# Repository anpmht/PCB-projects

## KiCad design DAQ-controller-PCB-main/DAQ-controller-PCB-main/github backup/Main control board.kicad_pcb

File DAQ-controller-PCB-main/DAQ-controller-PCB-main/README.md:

# DAQ-controller-PCB
### main controller - teenssy_4.1
### mux IC - 74HCT154PW
### Controls 16 channel analog amplifier and four ADC using  74HCT154PW multiplexer.

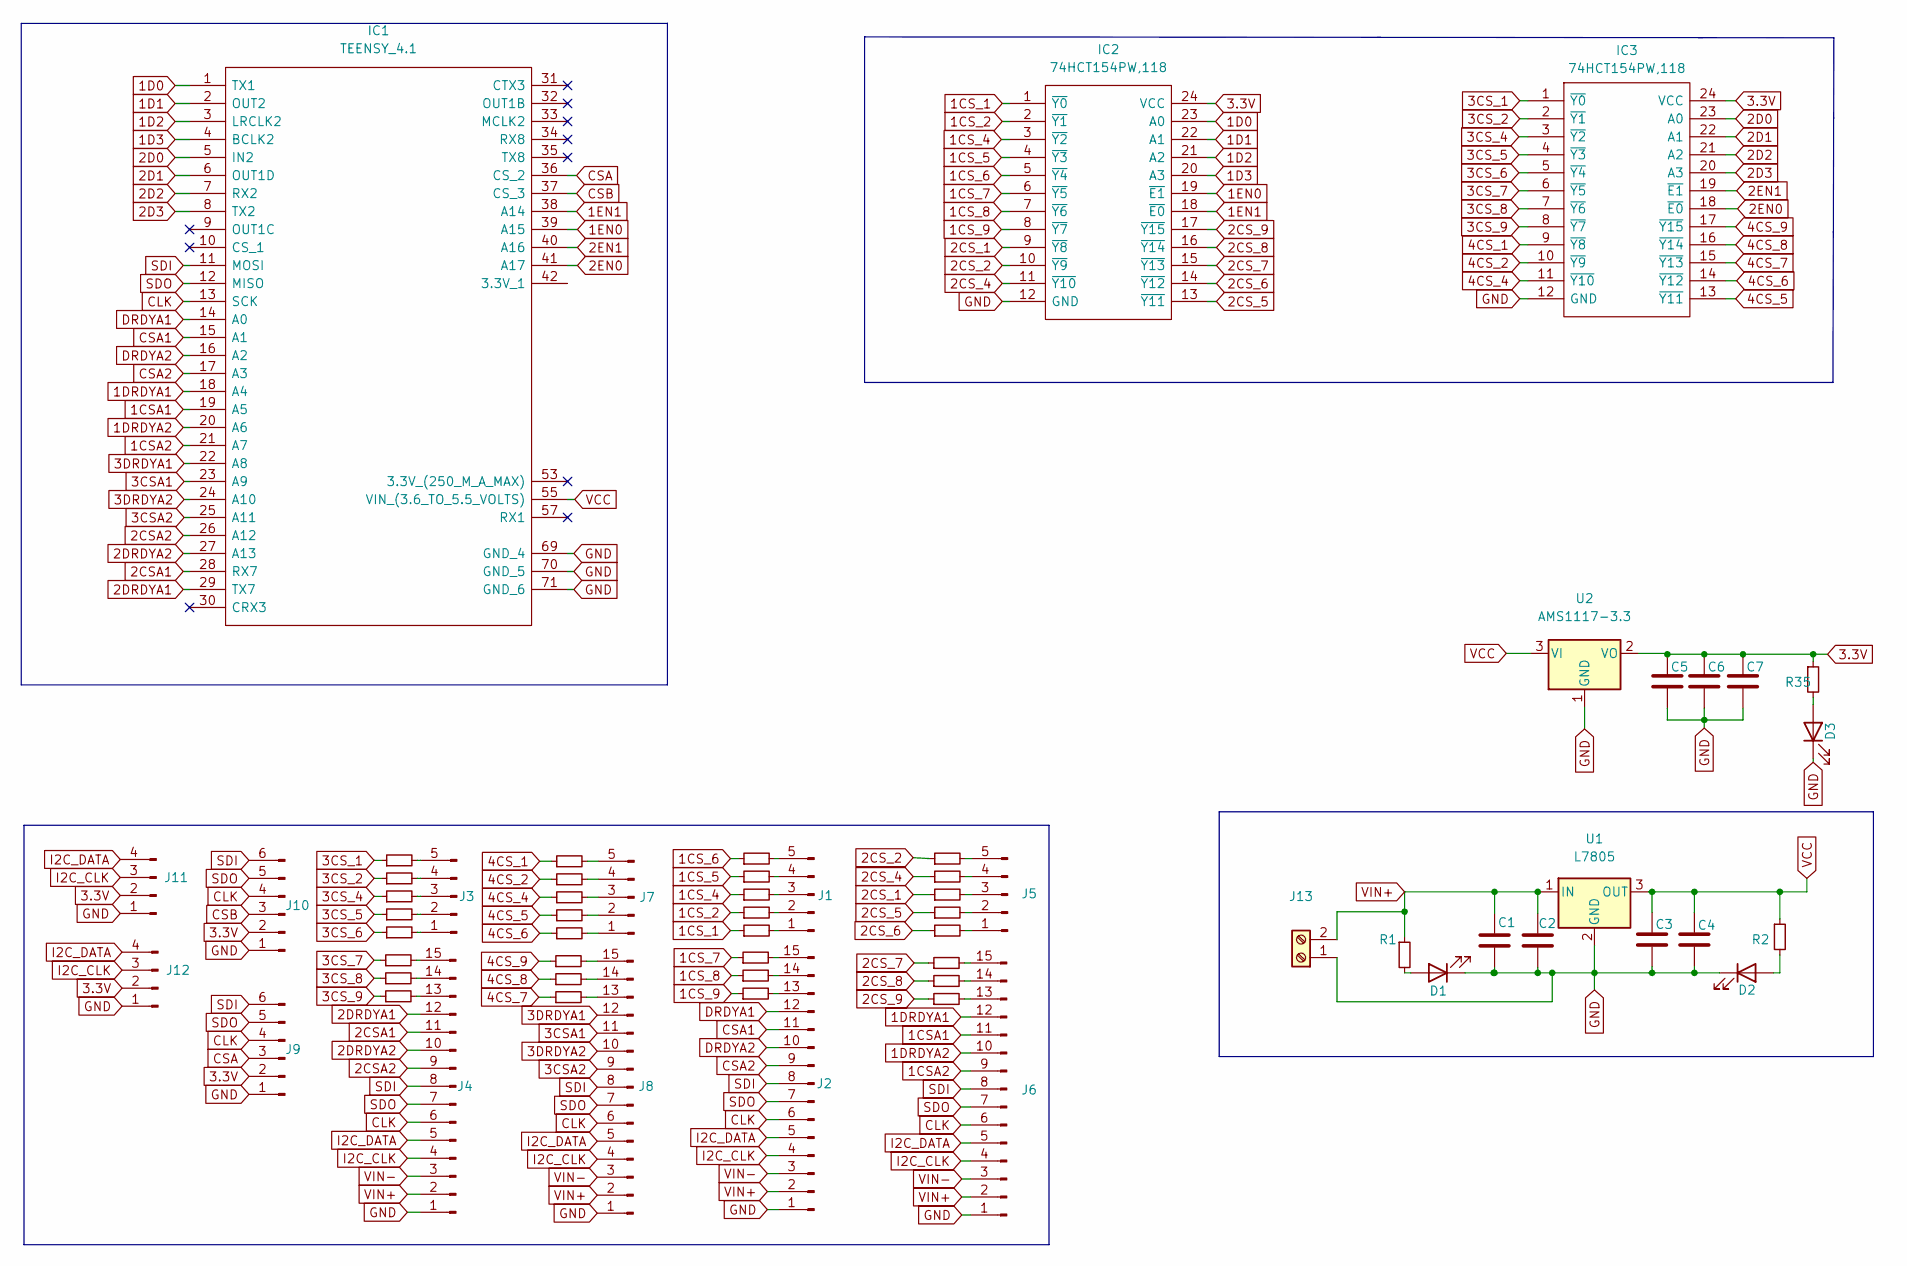
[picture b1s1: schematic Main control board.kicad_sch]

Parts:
C1, C3: 10uf; C_0805_2012Metric
C2, C4, C5, C6, C7: 1uf; C_0603_1608Metric
D1, D2, D3: LED; LED_0603_1608Metric
IC1: TEENSY_4.1; TEENSY41; Manufacturer_Part_Number TEENSY 4.1
IC2, IC3: 74HCT154PW,118; SOP65P640X110-24N; Manufacturer_Part_Number 74HCT154PW,118; Mouser Part Number 771-HCT154PW118
J1, J3, J5, J7: Conn_01x05_Male; JST_EH_B5B-EH-A_1x05_P2.50mm_Vertical
J2, J4, J6, J8: Conn_01x15_Male; JST_EH_B15B-EH-A_1x15_P2.50mm_Vertical
J9, J10: Conn_01x06_Male; JST_EH_B6B-EH-A_1x06_P2.50mm_Vertical
J11, J12: Conn_01x04_Male; JST_EH_B4B-EH-A_1x04_P2.50mm_Vertical
J13: (no value)
R1, R2, R35: 1.5k; R_0603_1608Metric
R3, R4, R5, R6, R7, R8, R9, R10, R11, R12, R13, R14, R15, R16, R17, R18, R19, R20, R21, R22, R23, R24, R25, R26, R27, R28, R29, R30, R31, R32, R33, R34: 470; R_0603_1608Metric
U1: L7805; TO228P972X240-3N
U2: AMS1117-3.3; SOT-223-3_TabPin2

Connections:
1CSA1: IC1.19 (A5), J6.11
1CSA2: IC1.21 (A7), J6.9
1CS_1: IC2.1 (~Y0), R26.1
1CS_2: IC2.2 (~Y1), R25.1
1CS_4: IC2.3 (~Y2), R24.1
1CS_5: IC2.4 (~Y3), R23.1
1CS_6: IC2.5 (~Y4), R22.1
1CS_7: IC2.6 (~Y5), R19.1
1CS_8: IC2.7 (~Y6), R20.1
1CS_9: IC2.8 (~Y7), R21.1
1D0: IC1.1 (TX1), IC2.23 (A0)
1D1: IC1.2 (OUT2), IC2.22 (A1)
1D2: IC1.3 (LRCLK2), IC2.21 (A2)
1D3: IC1.4 (BCLK2), IC2.20 (A3)
1DRDYA1: IC1.18 (A4), J6.12
1DRDYA2: IC1.20 (A6), J6.10
1EN0: IC1.39 (A15), IC2.19 (~E1)
1EN1: IC1.38 (A14), IC2.18 (~E0)
2CSA1: IC1.28 (RX7), J4.11
2CSA2: IC1.26 (A12), J4.9
2CS_1: IC2.9 (~Y8), R32.1
2CS_2: IC2.10 (~Y9), R30.1
2CS_4: IC2.11 (~Y10), R31.1
2CS_5: IC2.13 (~Y11), R33.1
2CS_6: IC2.14 (~Y12), R34.1
2CS_7: IC2.15 (~Y13), R27.1
2CS_8: IC2.16 (~Y14), R28.1
2CS_9: IC2.17 (~Y15), R29.1
2D0: IC1.5 (IN2), IC3.23 (A0)
2D1: IC1.6 (OUT1D), IC3.22 (A1)
2D2: IC1.7 (RX2), IC3.21 (A2)
2D3: IC1.8 (TX2), IC3.20 (A3)
2DRDYA1: IC1.29 (TX7), J4.12
2DRDYA2: IC1.27 (A13), J4.10
2EN0: IC1.41 (A17), IC3.18 (~E0)
2EN1: IC1.40 (A16), IC3.19 (~E1)
3.3V: C5.1, C6.1, C7.1, IC2.24 (VCC), IC3.24 (VCC), J9.2, J10.2, J11.2, J12.2, R35.1, U2.2 (VO)
3CSA1: IC1.23 (A9), J8.11
3CSA2: IC1.25 (A11), J8.9
3CS_1: IC3.1 (~Y0), R6.1
3CS_2: IC3.2 (~Y1), R7.1
3CS_4: IC3.3 (~Y2), R8.1
3CS_5: IC3.4 (~Y3), R9.1
3CS_6: IC3.5 (~Y4), R10.1
3CS_7: IC3.6 (~Y5), R3.1
3CS_8: IC3.7 (~Y6), R4.1
3CS_9: IC3.8 (~Y7), R5.1
3DRDYA1: IC1.22 (A8), J8.12
3DRDYA2: IC1.24 (A10), J8.10
4CS_1: IC3.9 (~Y8), R14.1
4CS_2: IC3.10 (~Y9), R15.1
4CS_4: IC3.11 (~Y10), R16.1
4CS_5: IC3.13 (~Y11), R17.1
4CS_6: IC3.14 (~Y12), R18.1
4CS_7: IC3.15 (~Y13), R13.1
4CS_8: IC3.16 (~Y14), R12.1
4CS_9: IC3.17 (~Y15), R11.1
CLK: IC1.13 (SCK), J2.6, J4.6, J6.6, J8.6, J9.4, J10.4
CSA: IC1.36 (CS_2), J9.3
CSA1: IC1.15 (A1), J2.11
CSA2: IC1.17 (A3), J2.9
CSB: IC1.37 (CS_3), J10.3
DRDYA1: IC1.14 (A0), J2.12
DRDYA2: IC1.16 (A2), J2.10
GND: C1.2, C2.2, C3.2, C4.2, C5.2, C6.2, C7.2, D1.1 (K), D2.1 (K), D3.1 (K), IC1.69 (GND_4), IC1.70 (GND_5), IC1.71 (GND_6), IC2.12 (GND), IC3.12 (GND), J2.1, J4.1, J6.1, J8.1, J9.1, J10.1, J11.1, J12.1, J13.1, U1.2 (GND), U2.1 (GND)
I2C_CLK: J2.4, J4.4, J6.4, J8.4, J11.3, J12.3
I2C_DATA: J2.5, J4.5, J6.5, J8.5, J11.4, J12.4
unnamed: D1.2 (A), R1.2
unnamed: D2.2 (A), R2.2
unnamed: D3.2 (A), R35.2
unnamed: J1.1, R26.2
unnamed: J1.2, R25.2
unnamed: J1.3, R24.2
unnamed: J1.4, R23.2
unnamed: J1.5, R22.2
unnamed: J2.13, R21.2
unnamed: J2.14, R20.2
unnamed: J2.15, R19.2
unnamed: J3.1, R10.2
unnamed: J3.2, R9.2
unnamed: J3.3, R8.2
unnamed: J3.4, R7.2
unnamed: J3.5, R6.2
unnamed: J4.13, R5.2
unnamed: J4.14, R4.2
unnamed: J4.15, R3.2
unnamed: J5.1, R34.2
unnamed: J5.2, R33.2
unnamed: J5.3, R32.2
unnamed: J5.4, R31.2
unnamed: J5.5, R30.2
unnamed: J6.13, R29.2
unnamed: J6.14, R28.2
unnamed: J6.15, R27.2
unnamed: J7.1, R18.2
unnamed: J7.2, R17.2
unnamed: J7.3, R16.2
unnamed: J7.4, R15.2
unnamed: J7.5, R14.2
unnamed: J8.13, R13.2
unnamed: J8.14, R12.2
unnamed: J8.15, R11.2
SDI: IC1.11 (MOSI), J2.8, J4.8, J6.8, J8.8, J9.6, J10.6
SDO: IC1.12 (MISO), J2.7, J4.7, J6.7, J8.7, J9.5, J10.5
VCC: C3.1, C4.1, IC1.55 (VIN_(3.6_TO_5.5_VOLTS)), R2.1, U1.3 (OUT), U2.3 (VI)
VIN+: C1.1, C2.1, J2.2, J4.2, J6.2, J8.2, J13.2, R1.1, U1.1 (IN)
VIN-: J2.3, J4.3, J6.3, J8.3

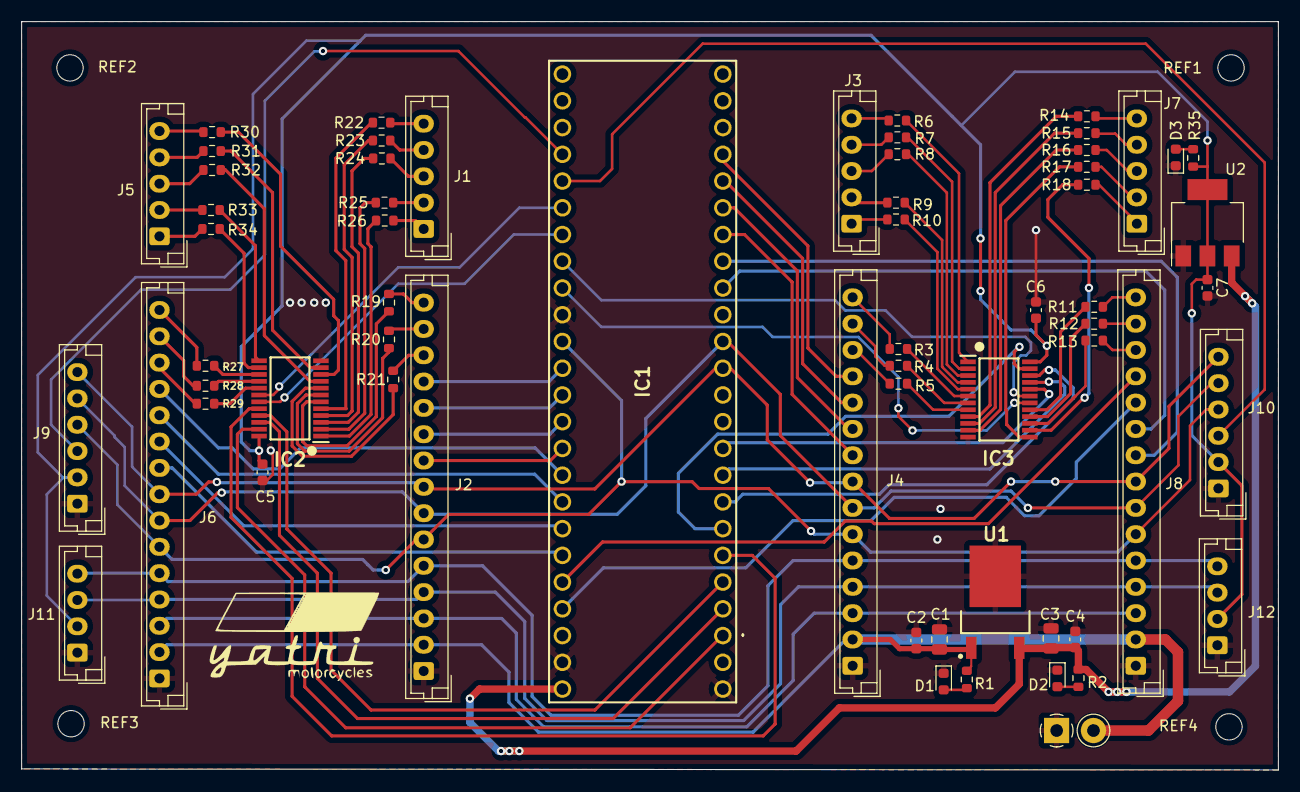
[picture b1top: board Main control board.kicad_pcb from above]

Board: 2 copper layers, 119.4 x 71.1 mm, 67 parts (0 on the bottom side), 107 nets.

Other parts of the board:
REF1, REF2, REF3, REF4: MountingHole_2.5mm

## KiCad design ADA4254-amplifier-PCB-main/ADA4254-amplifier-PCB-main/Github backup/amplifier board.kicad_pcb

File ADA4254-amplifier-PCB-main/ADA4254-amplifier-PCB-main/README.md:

# ADA4254-amplifier-PCB
ADA4254 precision amplifier PCB board

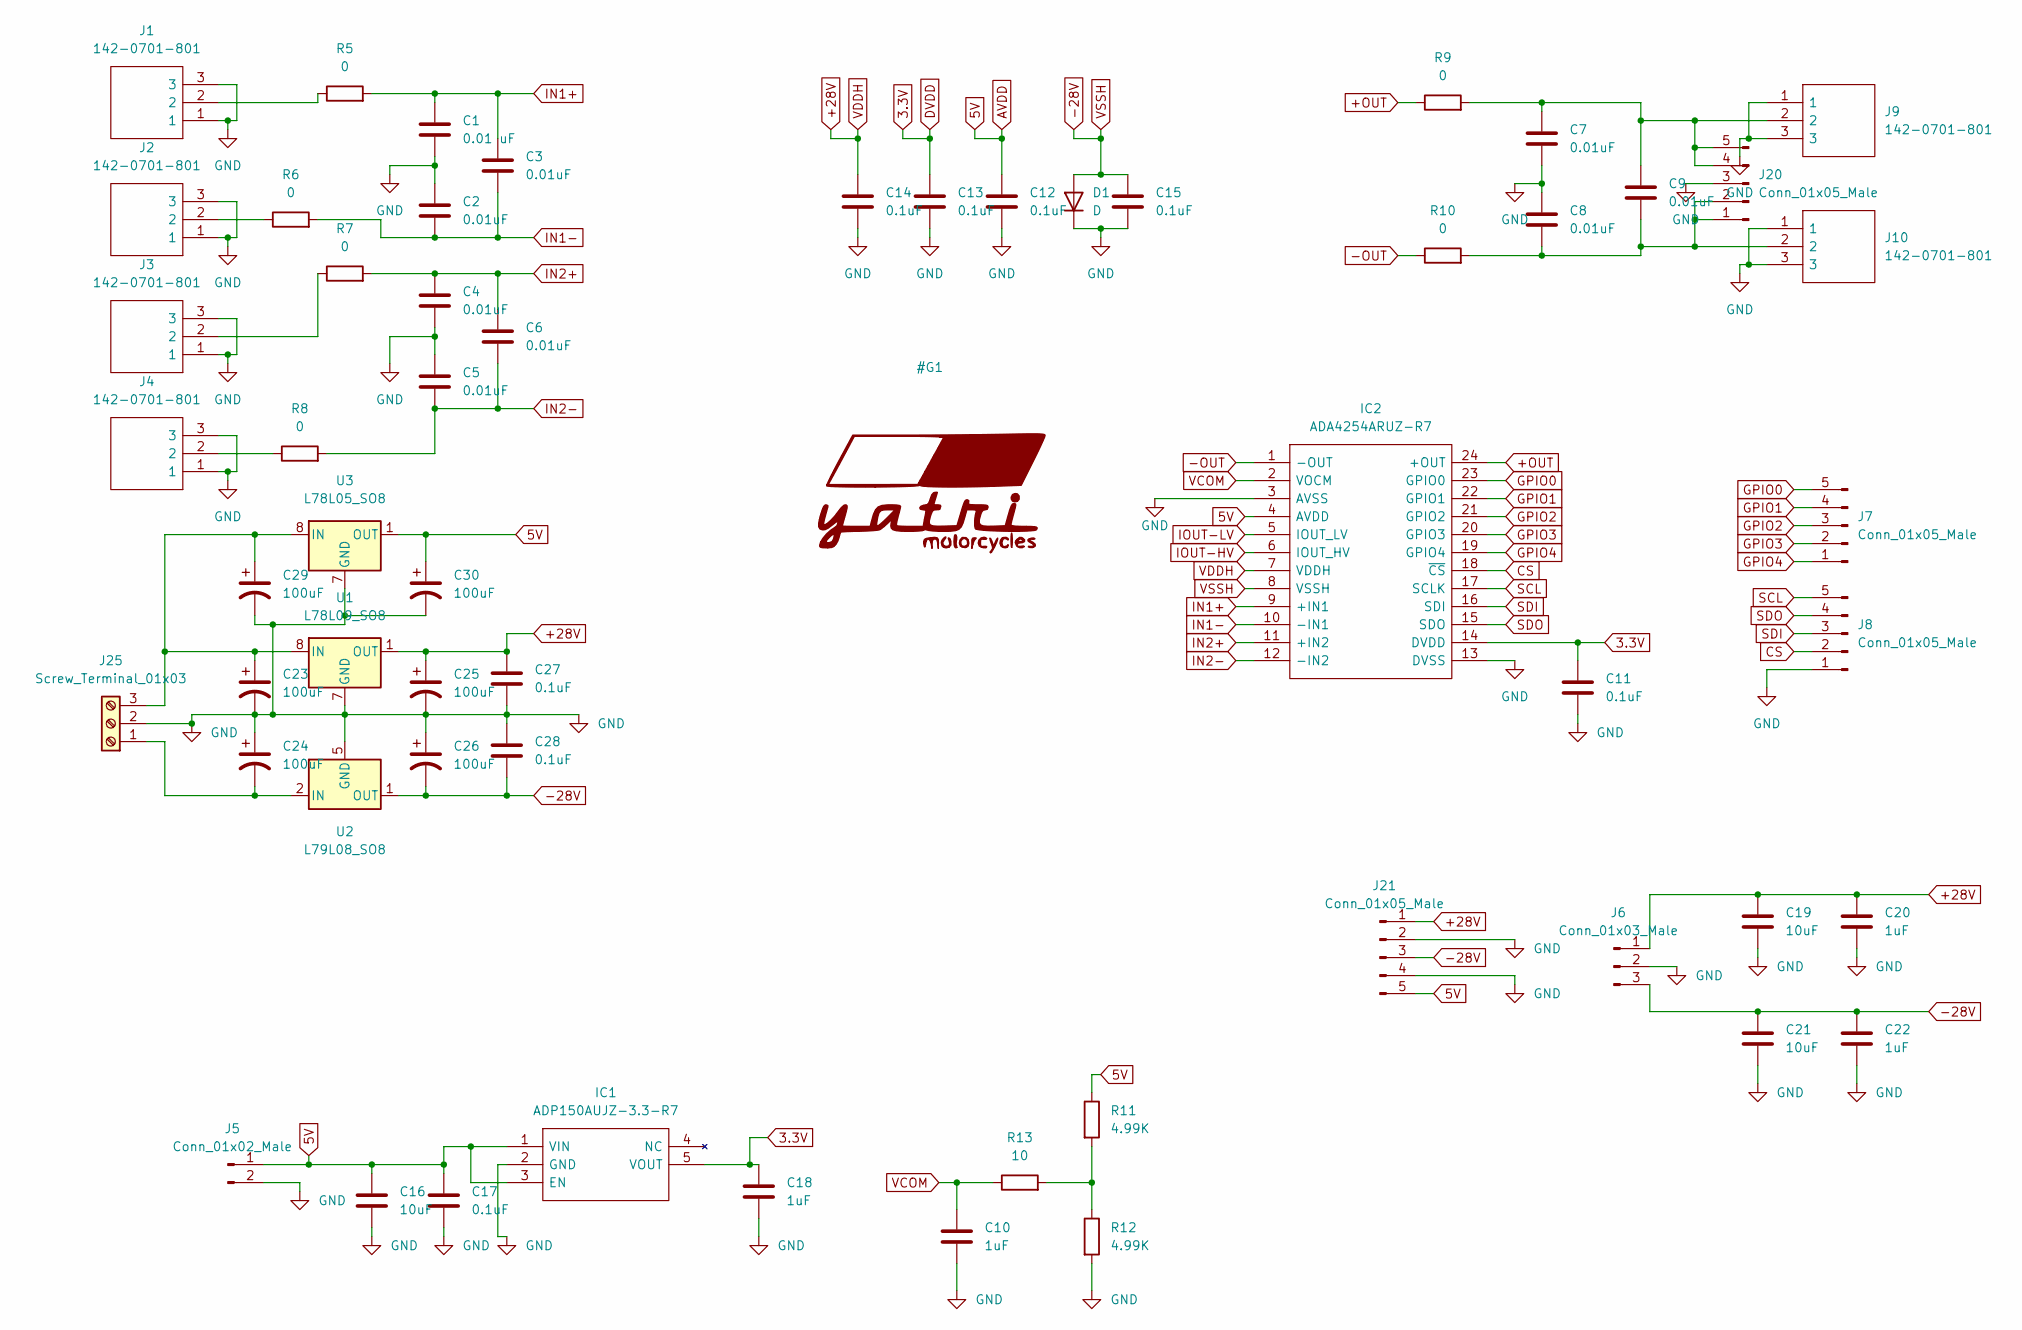
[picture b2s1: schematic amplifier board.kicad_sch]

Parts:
C1: 0.01 uF; C_0603_1608Metric_Pad1.08x0.95mm_HandSolder
C2, C3, C4, C5, C6, C7, C8, C9: 0.01uF; C_0603_1608Metric_Pad1.08x0.95mm_HandSolder
C10, C18, C20, C22: 1uF; C_0603_1608Metric_Pad1.08x0.95mm_HandSolder
C11, C12, C13, C14, C15, C17, C27, C28: 0.1uF; C_0603_1608Metric_Pad1.08x0.95mm_HandSolder
C16, C19, C21: 10uF; C_0805_2012Metric_Pad1.18x1.45mm_HandSolder
C23, C24, C25, C26, C29, C30: 100uF; CP_Radial_D6.3mm_P2.50mm
D1: D; D_0603_1608Metric_Pad1.05x0.95mm_HandSolder
IC1: ADP150AUJZ-3.3-R7; SOT95P280X100-5N; Manufacturer_Part_Number ADP150AUJZ-3.3-R7; Mouser Part Number N/A
IC2: ADA4254ARUZ-R7; SOP65P640X120-24N; Manufacturer_Part_Number ADA4254ARUZ-R7; Mouser Part Number 584-ADA4254ARUZ-R7
J1, J2, J3, J4, J9, J10: 142-0701-801; 142-0701-851; Manufacturer_Part_Number 142-0701-801; Mouser Part Number 530-142-0701-801
J5: Conn_01x02_Male; PinSocket_1x02_P2.54mm_Vertical
J6: Conn_01x03_Male; PinSocket_1x03_P2.54mm_Vertical
J7, J8, J21: Conn_01x05_Male; PinSocket_1x05_P2.54mm_Vertical
J20: Conn_01x05_Male; PinHeader_1x05_P2.54mm_Vertical
J25: Screw_Terminal_01x03; TerminalBlock_Philmore_TB133_1x03_P5.00mm_Horizontal
R5, R6, R7, R8, R9, R10: 0; R_0603_1608Metric_Pad0.98x0.95mm_HandSolder
R11, R12: 4.99K; R_0603_1608Metric_Pad0.98x0.95mm_HandSolder
R13: 10; R_0603_1608Metric_Pad0.98x0.95mm_HandSolder
U1: L78L09_SO8; SOIC-8_3.9x4.9mm_P1.27mm
U2: L79L08_SO8; SOIC-8_3.9x4.9mm_P1.27mm
U3: L78L05_SO8; SOIC-8_3.9x4.9mm_P1.27mm

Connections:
3.3V: C11.2, C13.1, C18.1, IC1.5 (VOUT), IC2.14 (DVDD)
5V: C12.1, C16.1, C17.1, C30.1, IC1.1 (VIN), IC1.3 (EN), IC2.4 (AVDD), J5.1, J21.5, R11.1, U3.1 (OUT)
+28V: C14.1, C19.2, C20.2, C25.1, C27.1, IC2.7 (VDDH), J6.1, J21.1, U1.1 (OUT)
+OUT: IC2.24 (+OUT), R9.1
-28V: C15.1, C21.2, C22.2, C26.2, C28.2, D1.2 (A), IC2.8 (VSSH), J6.3, J21.3, U2.1 (OUT)
-OUT: IC2.1 (-OUT), R10.1
CS: IC2.18 (~CS), J8.2
GND: C1.2, C2.1, C4.2, C5.1, C7.2, C8.1, C10.1, C11.1, C12.2, C13.2, C14.2, C15.2, C16.2, C17.2, C18.2, C19.1, C20.1, C21.1, C22.1, C23.2, C24.1, C25.2, C26.1, C27.2, C28.1, C29.2, C30.2, D1.1 (K), IC1.2 (GND), IC2.3 (AVSS), IC2.13 (DVSS), J1.1, J1.3, J2.1, J2.3, J3.1, J3.3, J4.1, J4.3, J5.2, J6.2, J8.1, J9.1, J9.3, J10.1, J10.3, J20.3, J21.2, J21.4, J25.2, R12.2, U1.2 (GND), U1.3 (GND), U1.6 (GND), U1.7 (GND), U2.5 (GND), U3.2 (GND), U3.3 (GND), U3.6 (GND), U3.7 (GND)
GPIO0: IC2.23 (GPIO0), J7.5
GPIO1: IC2.22 (GPIO1), J7.4
GPIO2: IC2.21 (GPIO2), J7.3
GPIO3: IC2.20 (GPIO3), J7.2
GPIO4: IC2.19 (GPIO4), J7.1
IN1+: C1.1, C3.1, IC2.9 (+IN1), R5.2
IN1-: C2.2, C3.2, IC2.10 (-IN1), R6.2
IN2+: C4.1, C6.1, IC2.11 (+IN2), R7.2
IN2-: C5.2, C6.2, IC2.12 (-IN2), R8.2
IOUT-HV: IC2.6 (IOUT_HV)
IOUT-LV: IC2.5 (IOUT_LV)
unnamed: C7.1, C9.1, J9.2, J20.4, J20.5, R9.2
unnamed: C8.2, C9.2, J10.2, J20.1, J20.2, R10.2
unnamed: C23.1, C29.1, J25.3, U1.8 (IN), U3.8 (IN)
unnamed: C24.2, J25.1, U2.2 (IN), U2.3 (IN), U2.6 (IN), U2.7 (IN)
unnamed: J1.2, R5.1
unnamed: J2.2, R6.1
unnamed: J3.2, R7.1
unnamed: J4.2, R8.1
unnamed: R11.2, R12.1, R13.2
SCL: IC2.17 (SCLK), J8.5
SDI: IC2.16 (SDI), J8.3
SDO: IC2.15 (SDO), J8.4
VCOM: C10.2, IC2.2 (VOCM), R13.1

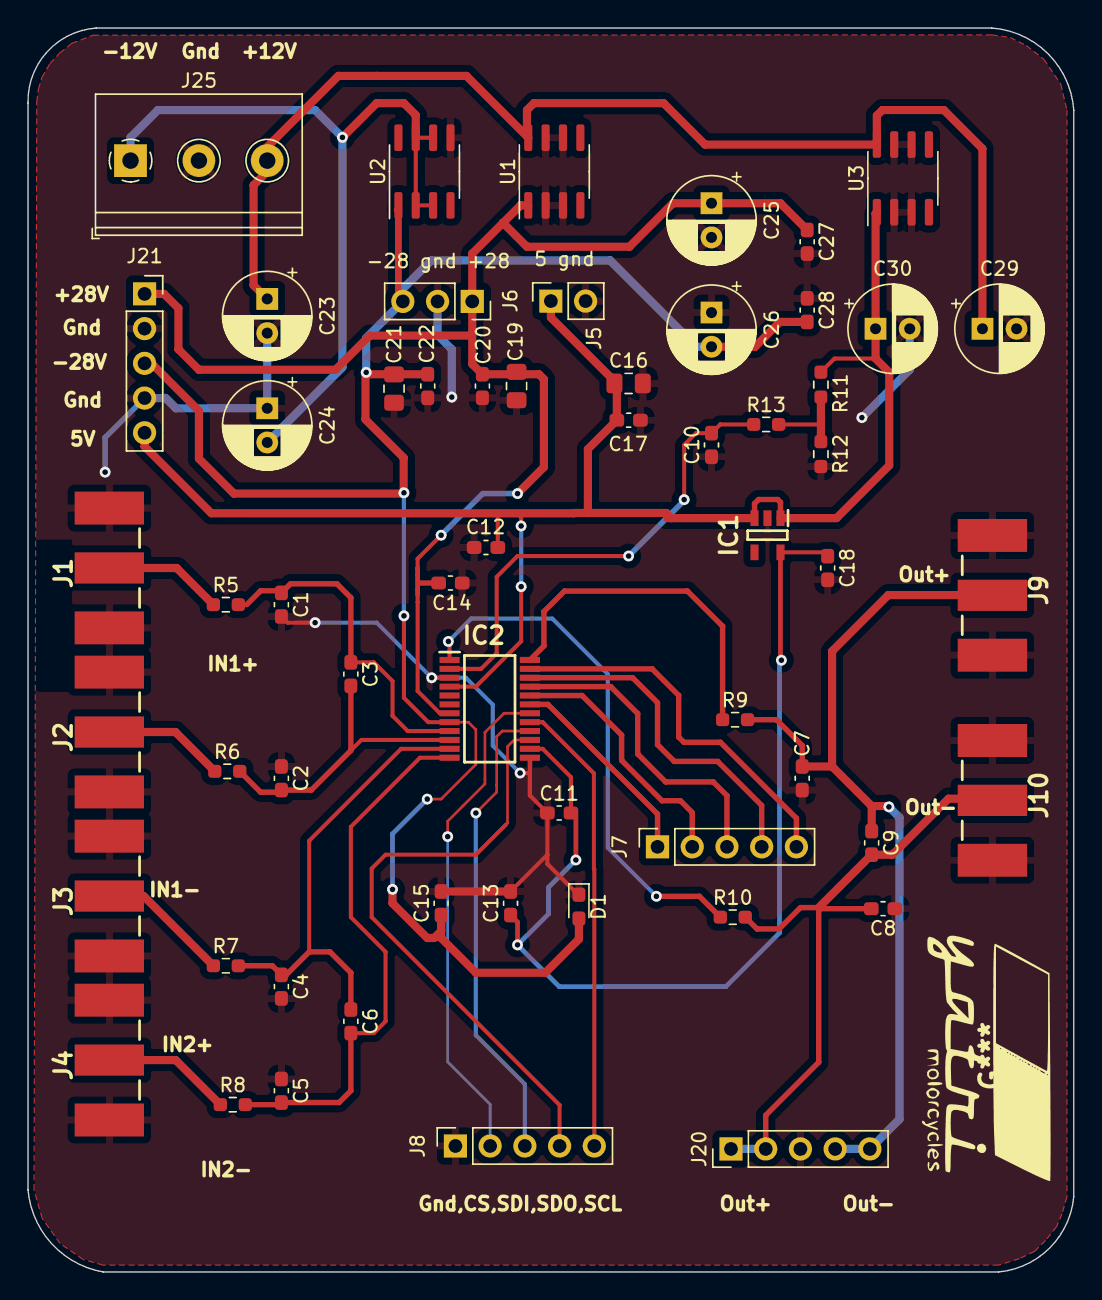
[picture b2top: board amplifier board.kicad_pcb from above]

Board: 2 copper layers, 76.5 x 91.0 mm, 58 parts (0 on the bottom side), 30 nets.

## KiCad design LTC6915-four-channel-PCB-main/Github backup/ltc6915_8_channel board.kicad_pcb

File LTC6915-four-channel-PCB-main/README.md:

# LTC6915-four-channel-PCB
four channel precision amplifier board using ltc6915 instrumentation amplifier

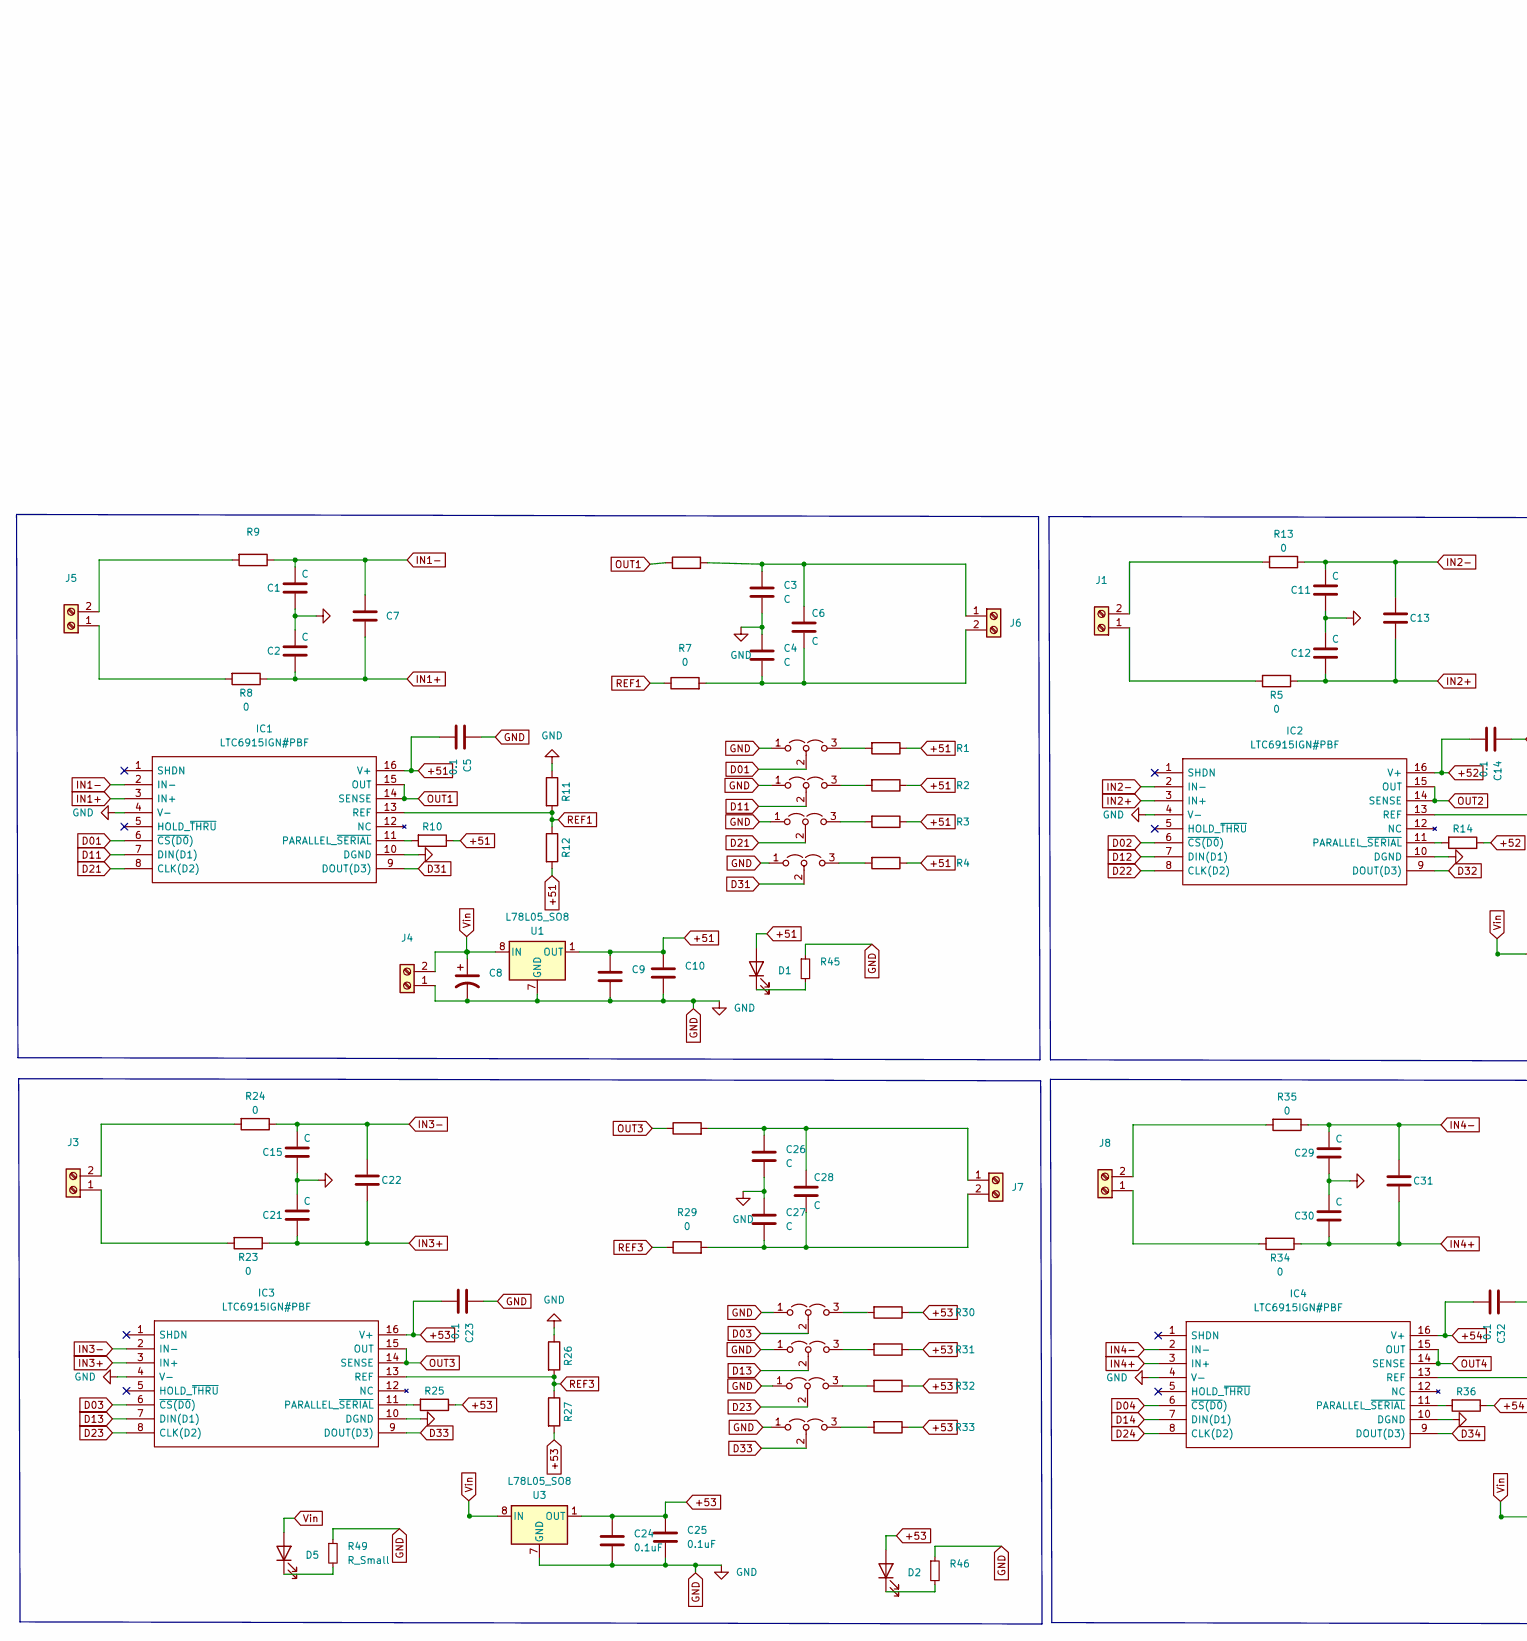
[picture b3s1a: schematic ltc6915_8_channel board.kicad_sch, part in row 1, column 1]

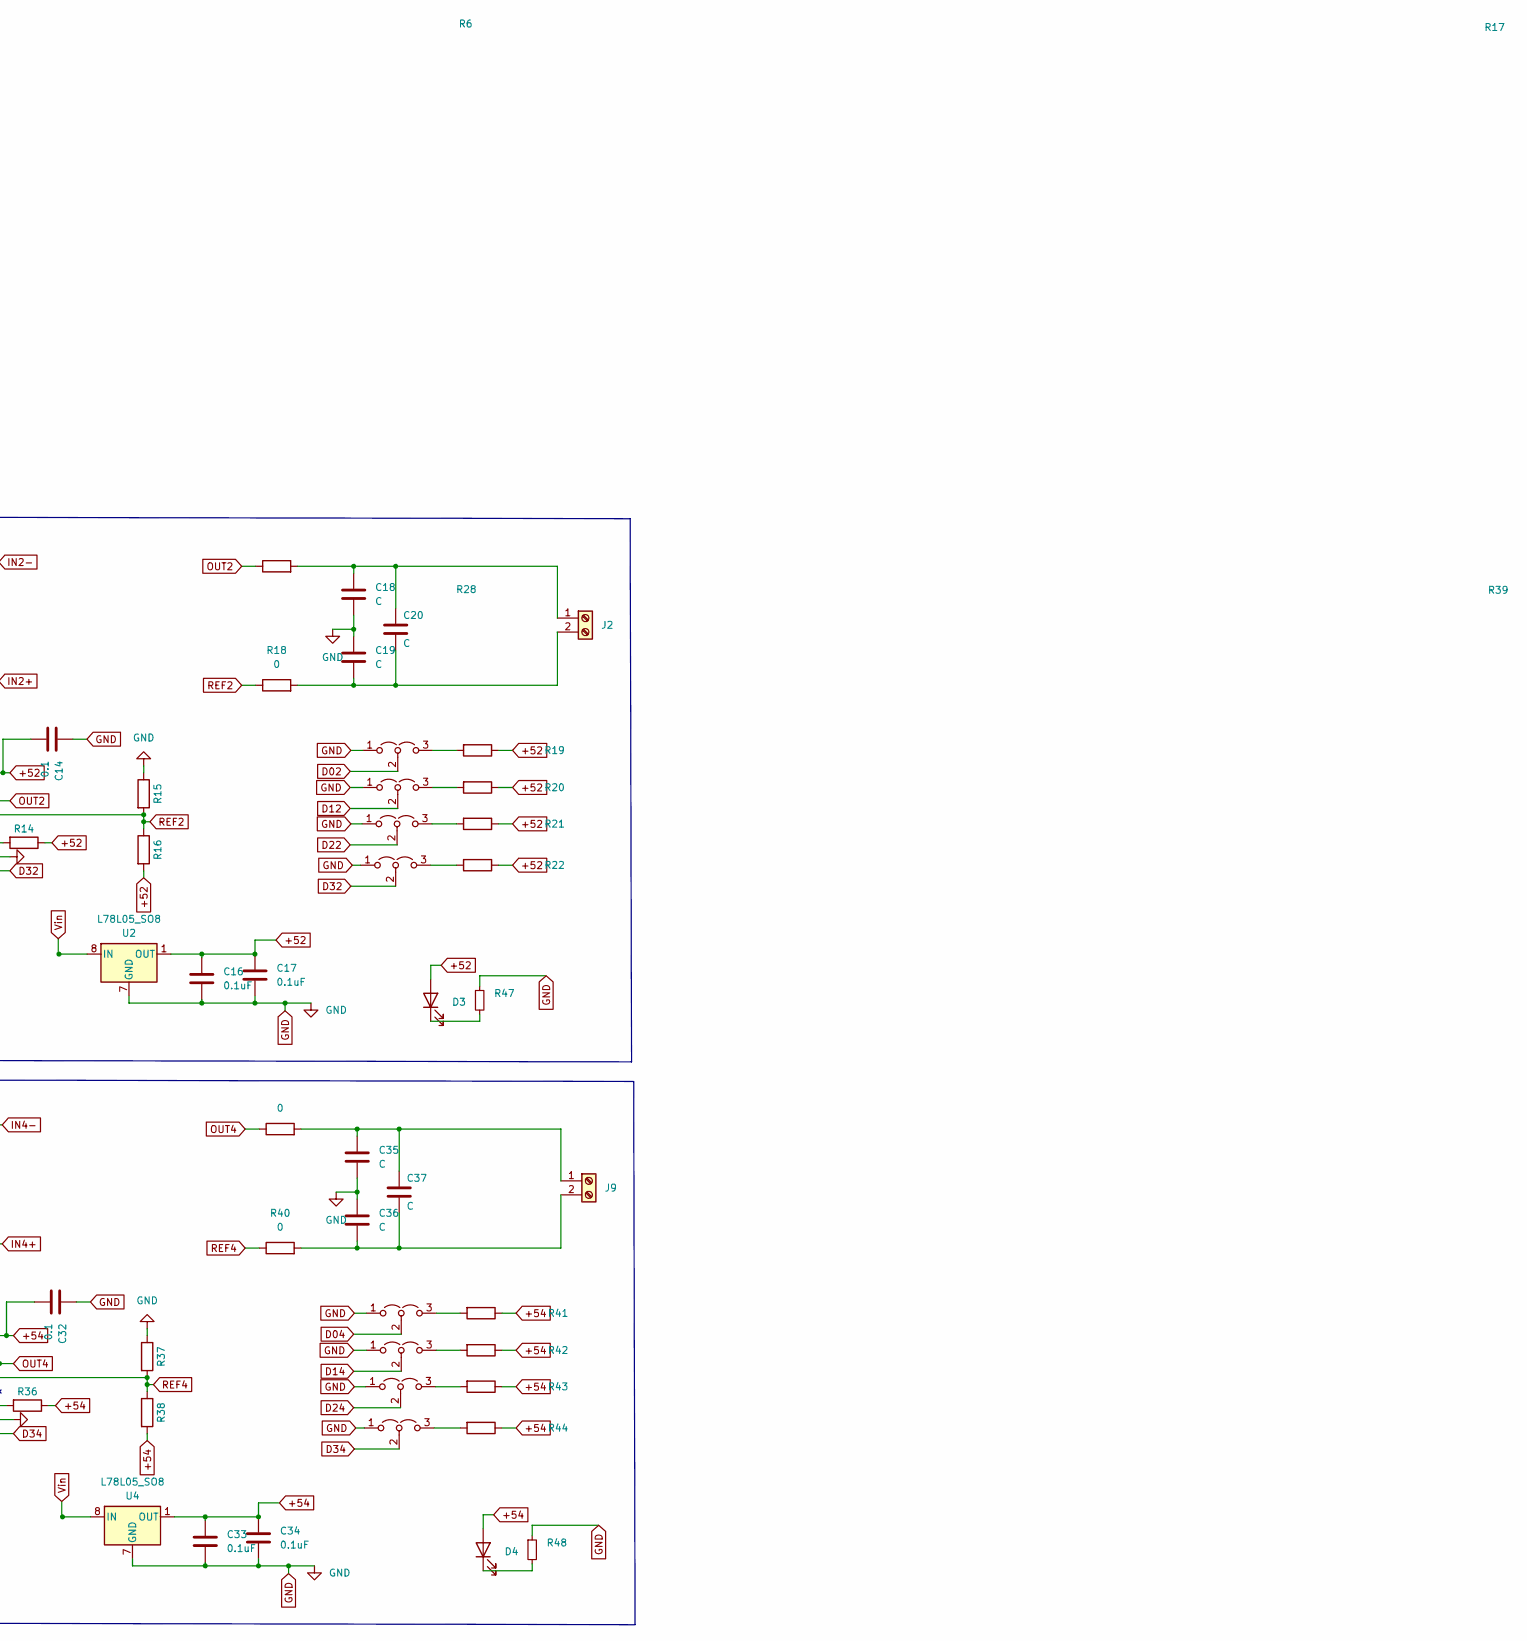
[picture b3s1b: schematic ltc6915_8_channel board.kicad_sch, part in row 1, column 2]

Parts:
C1, C2, C3, C4, C6, C7, C11, C12, C13, C15, C18, C19, C20, C21, C22, C26, C27, C28, C29, C30, C31, C35, C36, C37: C; C_0603_1608Metric_Pad1.08x0.95mm_HandSolder
C5, C14, C23, C32: 0.1; C_0603_1608Metric_Pad1.08x0.95mm_HandSolder
C8, C9, C10: (no value)
C16, C24, C33: 0.1uF; C_0805_2012Metric
C17, C25, C34: 0.1uF; C_0603_1608Metric_Pad1.08x0.95mm_HandSolder
D1, D2, D3, D4: (no value)
D5: LED; LED_0603_1608Metric_Pad1.05x0.95mm_HandSolder
IC1, IC2, IC3, IC4: LTC6915IGN#PBF; SOP64P600X175-16N; Manufacturer_Part_Number LTC6915IGN#PBF; Mouser Part Number 584-LTC6915IGN#PBF
J1, J2, J3, J4, J6, J7, J8, J9: Screw_Terminal_01x02; TerminalBlock_Phoenix_MPT-0,5-2-2.54_1x02_P2.54mm_Horizontal
J5: (no value)
JP1, JP2, JP3, JP4, JP5, JP6, JP7, JP8, JP9, JP10, JP11, JP12, JP13, JP14, JP15, JP16: Jumper_3_Open; SolderJumper-3_P1.3mm_Open_RoundedPad1.0x1.5mm
R1, R2, R3, R4, R10, R14, R19, R20, R21, R22, R25, R30, R31, R32, R33, R36, R41, R42, R43, R44: 470; R_0603_1608Metric_Pad0.98x0.95mm_HandSolder
R5, R7, R8, R13, R18, R23, R24, R29, R34, R35, R39, R40: 0; R_0603_1608Metric_Pad0.98x0.95mm_HandSolder
R6, R9, R17, R28, R45, R46, R47, R48: (no value)
R11, R12, R15, R16, R26, R27, R37, R38: 4.7k; R_0603_1608Metric_Pad0.98x0.95mm_HandSolder
R49: R_Small; R_0603_1608Metric_Pad0.98x0.95mm_HandSolder
U1, U2, U3, U4: L78L05_SO8; SOIC-8_3.9x4.9mm_P1.27mm

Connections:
+51: C5.2, C9.1, C10.1, D1.2 (A), IC1.16 (V+), R1.1, R2.1, R3.1, R4.1, R10.1, R12.2, U1.1 (OUT)
+52: C14.2, C16.1, C17.1, D3.2 (A), IC2.16 (V+), R14.1, R16.2, R19.1, R20.1, R21.1, R22.1, U2.1 (OUT)
+53: C23.2, C24.1, C25.1, D2.2 (A), IC3.16 (V+), R25.1, R27.2, R30.1, R31.1, R32.1, R33.1, U3.1 (OUT)
+54: C32.2, C33.1, C34.1, D4.2 (A), IC4.16 (V+), R36.1, R38.2, R41.1, R42.1, R43.1, R44.1, U4.1 (OUT)
D01: IC1.6 (~CS(D0)), JP3.2 (C)
D02: IC2.6 (~CS(D0)), JP7.2 (C)
D03: IC3.6 (~CS(D0)), JP11.2 (C)
D04: IC4.6 (~CS(D0)), JP15.2 (C)
D11: IC1.7 (DIN(D1)), JP4.2 (C)
D12: IC2.7 (DIN(D1)), JP8.2 (C)
D13: IC3.7 (DIN(D1)), JP12.2 (C)
D14: IC4.7 (DIN(D1)), JP16.2 (C)
D21: IC1.8 (CLK(D2)), JP2.2 (C)
D22: IC2.8 (CLK(D2)), JP6.2 (C)
D23: IC3.8 (CLK(D2)), JP10.2 (C)
D24: IC4.8 (CLK(D2)), JP14.2 (C)
D31: IC1.9 (DOUT(D3)), JP1.2 (C)
D32: IC2.9 (DOUT(D3)), JP5.2 (C)
D33: IC3.9 (DOUT(D3)), JP9.2 (C)
D34: IC4.9 (DOUT(D3)), JP13.2 (C)
GND: C1.1, C2.2, C3.2, C4.1, C5.1, C8.2, C9.2, C10.2, C11.1, C12.2, C14.1, C15.1, C16.2, C17.2, C18.2, C19.1, C21.2, C23.1, C24.2, C25.2, C26.2, C27.1, C29.1, C30.2, C32.1, C33.2, C34.2, C35.2, C36.1, IC1.4 (V-), IC1.10 (DGND), IC2.4 (V-), IC2.10 (DGND), IC3.4 (V-), IC3.10 (DGND), IC4.4 (V-), IC4.10 (DGND), J4.1, JP1.1 (A), JP2.1 (A), JP3.1 (A), JP4.1 (A), JP5.1 (A), JP6.1 (A), JP7.1 (A), JP8.1 (A), JP9.1 (A), JP10.1 (A), JP11.1 (A), JP12.1 (A), JP13.1 (A), JP14.1 (A), JP15.1 (A), JP16.1 (A), R11.1, R15.1, R26.1, R37.1, R45.1, R46.1, R47.1, R48.1, R49.1, U1.2 (GND), U1.3 (GND), U1.6 (GND), U1.7 (GND), U2.2 (GND), U2.3 (GND), U2.6 (GND), U2.7 (GND), U3.2 (GND), U3.3 (GND), U3.6 (GND), U3.7 (GND), U4.2 (GND), U4.3 (GND), U4.6 (GND), U4.7 (GND)
IN1+: C2.1, C7.1, IC1.3 (IN+), R8.1
IN1-: C1.2, C7.2, IC1.2 (IN-), R9.1
IN2+: C12.1, C13.1, IC2.3 (IN+), R5.1
IN2-: C11.2, C13.2, IC2.2 (IN-), R13.1
IN3+: C21.1, C22.1, IC3.3 (IN+), R23.1
IN3-: C15.2, C22.2, IC3.2 (IN-), R24.1
IN4+: C30.1, C31.1, IC4.3 (IN+), R34.1
IN4-: C29.2, C31.2, IC4.2 (IN-), R35.1
unnamed: C3.1, C6.1, J6.1, R6.2
unnamed: C4.2, C6.2, J6.2, R7.2
unnamed: C18.1, C20.1, J2.1, R17.2
unnamed: C19.2, C20.2, J2.2, R18.2
unnamed: C26.1, C28.1, J7.1, R28.2
unnamed: C27.2, C28.2, J7.2, R29.2
unnamed: C35.1, C37.1, J9.1, R39.2
unnamed: C36.2, C37.2, J9.2, R40.2
unnamed: D1.1 (K), R45.2
unnamed: D2.1 (K), R46.2
unnamed: D3.1 (K), R47.2
unnamed: D4.1 (K), R48.2
unnamed: D5.1 (K), R49.2
unnamed: IC1.11 (PARALLEL_~SERIAL), R10.2
unnamed: IC2.11 (PARALLEL_~SERIAL), R14.2
unnamed: IC3.11 (PARALLEL_~SERIAL), R25.2
unnamed: IC4.11 (PARALLEL_~SERIAL), R36.2
unnamed: J1.1, R5.2
unnamed: J1.2, R13.2
unnamed: J3.1, R23.2
unnamed: J3.2, R24.2
unnamed: J5.1, R8.2
unnamed: J5.2, R9.2
unnamed: J8.1, R34.2
unnamed: J8.2, R35.2
unnamed: JP1.3 (B), R4.2
unnamed: JP2.3 (B), R3.2
unnamed: JP3.3 (B), R1.2
unnamed: JP4.3 (B), R2.2
unnamed: JP5.3 (B), R22.2
unnamed: JP6.3 (B), R21.2
unnamed: JP7.3 (B), R19.2
unnamed: JP8.3 (B), R20.2
unnamed: JP9.3 (B), R33.2
unnamed: JP10.3 (B), R32.2
unnamed: JP11.3 (B), R30.2
unnamed: JP12.3 (B), R31.2
unnamed: JP13.3 (B), R44.2
unnamed: JP14.3 (B), R43.2
unnamed: JP15.3 (B), R41.2
unnamed: JP16.3 (B), R42.2
OUT1: IC1.14 (SENSE), IC1.15 (OUT), R6.1
OUT2: IC2.14 (SENSE), IC2.15 (OUT), R17.1
OUT3: IC3.14 (SENSE), IC3.15 (OUT), R28.1
OUT4: IC4.14 (SENSE), IC4.15 (OUT), R39.1
REF1: IC1.13 (REF), R7.1, R11.2, R12.1
REF2: IC2.13 (REF), R15.2, R16.1, R18.1
REF3: IC3.13 (REF), R26.2, R27.1, R29.1
REF4: IC4.13 (REF), R37.2, R38.1, R40.1
Vin: C8.1, D5.2 (A), J4.2, U1.8 (IN), U2.8 (IN), U3.8 (IN), U4.8 (IN)

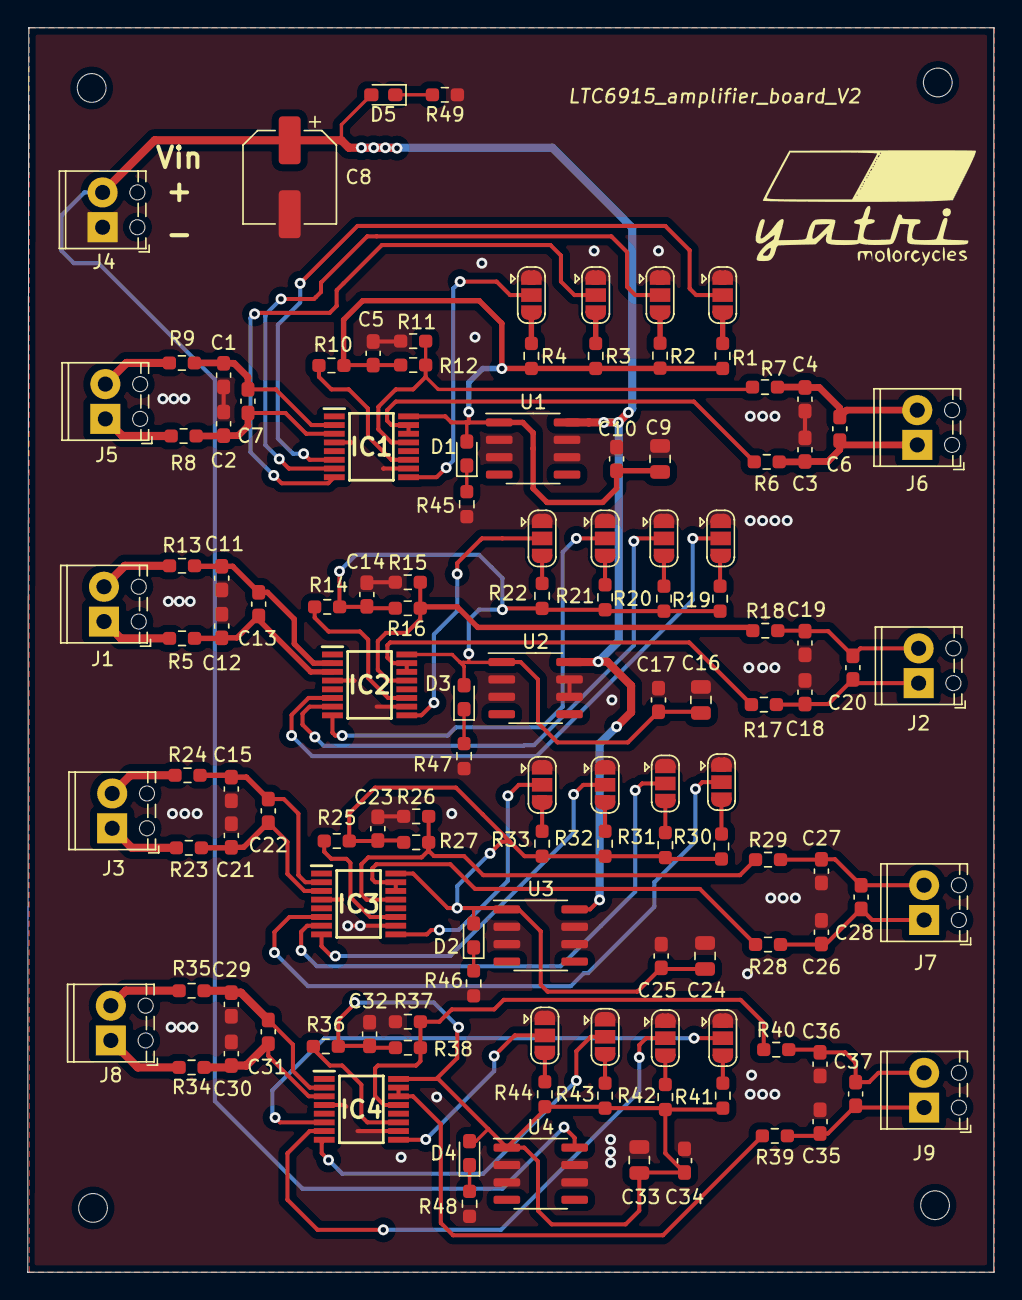
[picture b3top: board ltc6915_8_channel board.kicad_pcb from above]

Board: 2 copper layers, 70.6 x 90.9 mm, 124 parts (0 on the bottom side), 79 nets.
